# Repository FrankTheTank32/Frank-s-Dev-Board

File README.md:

This respository includes the bill of materials (BOM), GRBR and DRL files for PCB manufacturing and specifications, as well as the entire project folder itself for importing into KiCAD.

The DevBoard is comprised of an RP2040 microcontroller, lights, 43 pins total, an IMU, and a nice silkscreen design. It resembles the shape of an "F" after the name frame, and has the meming frog, as that also starts with an "F". This development board is extremely useful if you're looking to have a highly functional (and highly energetic) microcontroller electronics maker experience.

PCB design in 2D

PCB design in 3D

ENJOY!!!

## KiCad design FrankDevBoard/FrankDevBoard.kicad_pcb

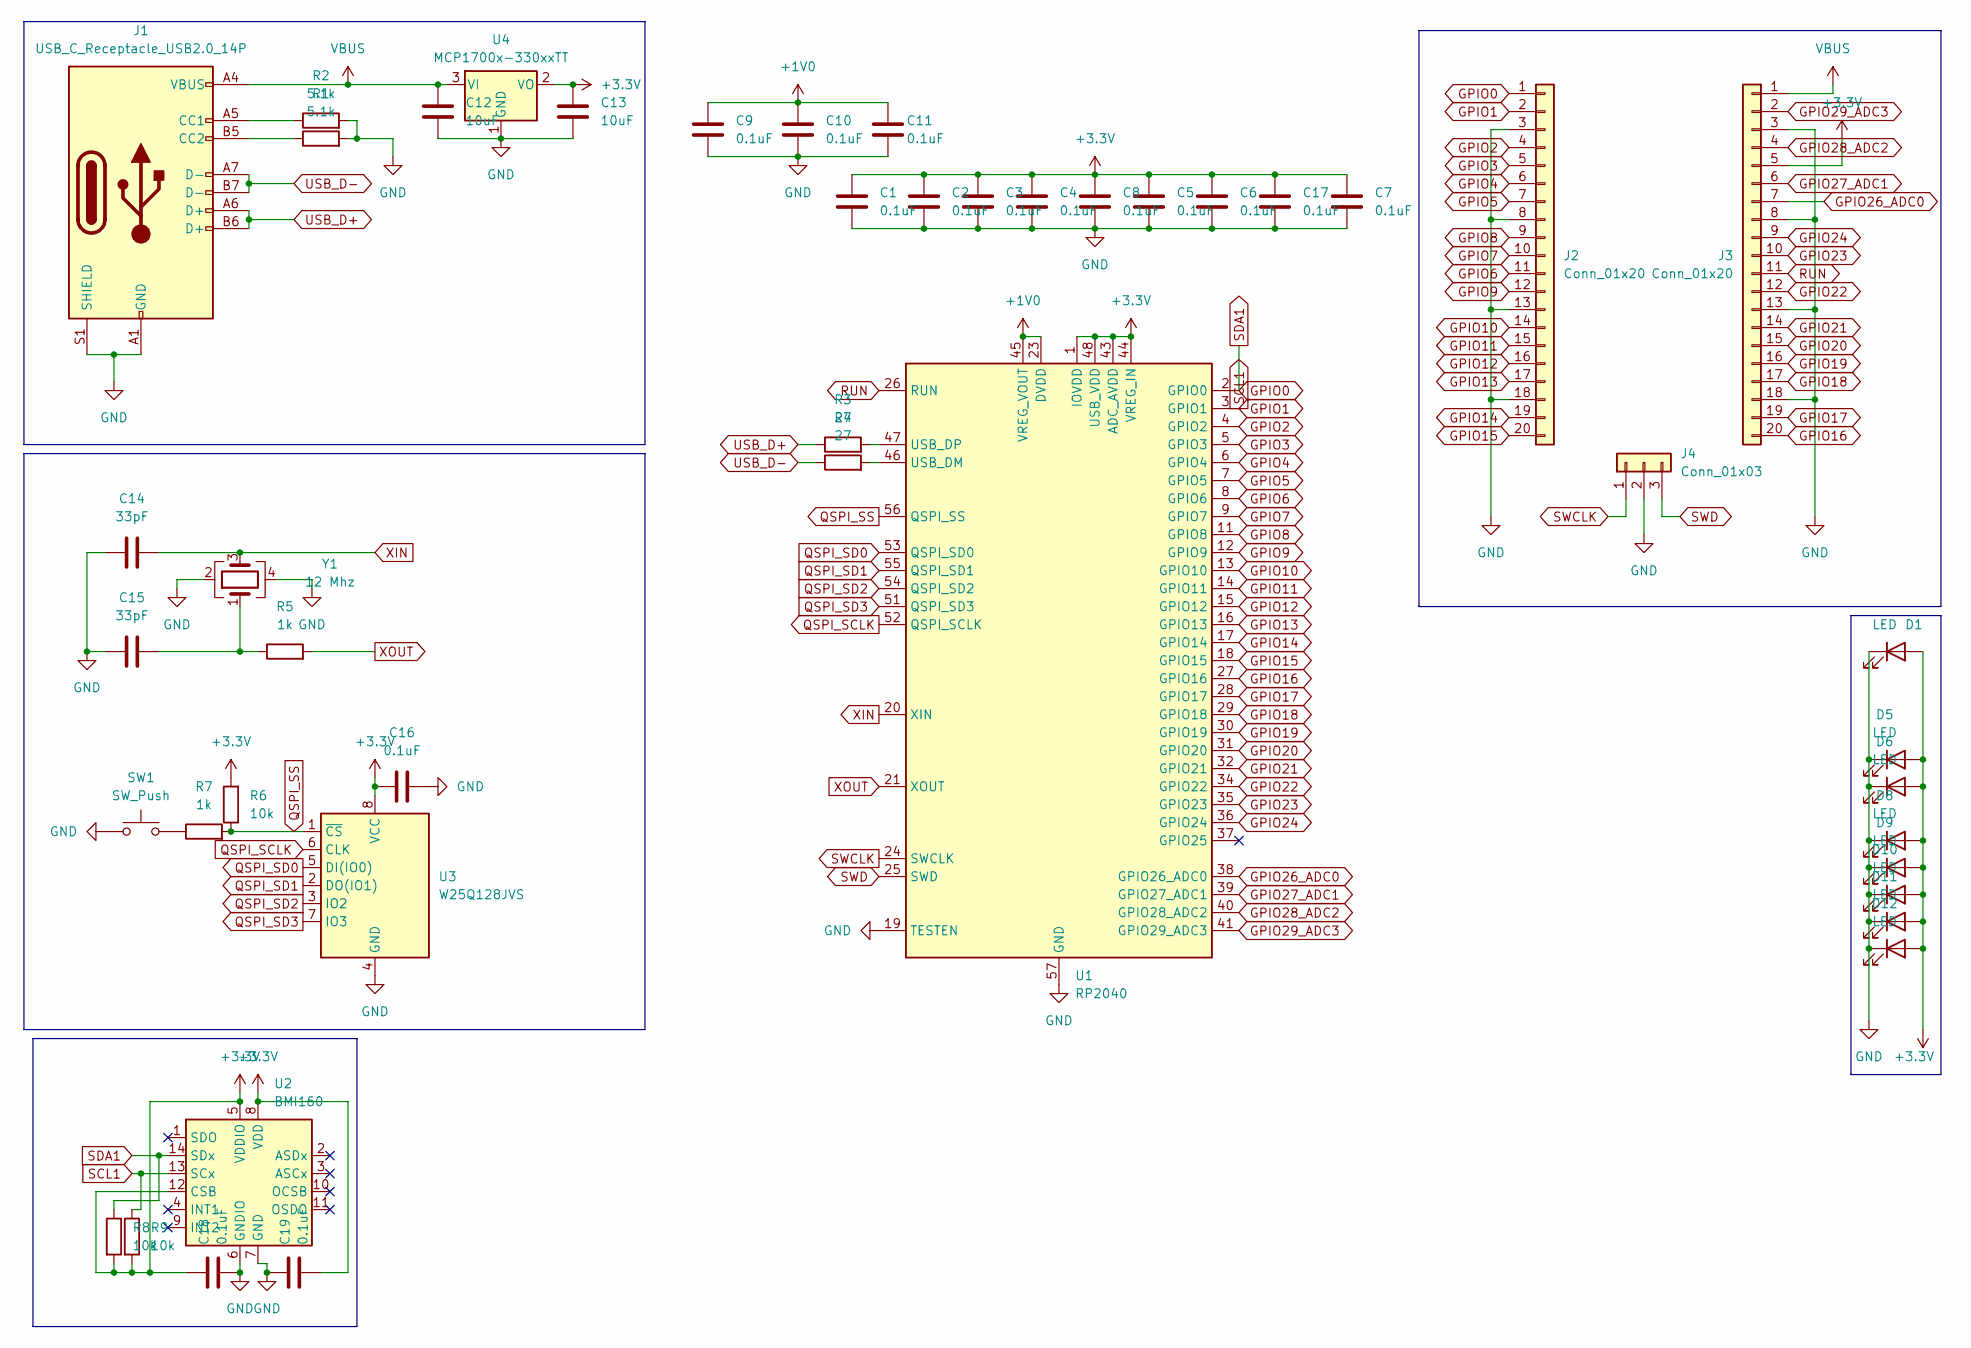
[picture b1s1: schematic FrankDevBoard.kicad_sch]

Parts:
C1, C2, C3, C4, C5, C6, C7, C8, C9, C10, C11, C16, C17, C18, C19: 0.1uF; C_0402_1005Metric
C12, C13: 10uF; C_0603_1608Metric
C14, C15: 33pF; C_0402_1005Metric
D1, D5, D6, D8, D9, D10, D11, D12: LED; LED_1210_3225Metric
J1: USB_C_Receptacle_USB2.0_14P; USB_C_Receptacle_HRO_TYPE-C-31-M-12
J2, J3: Conn_01x20; PinHeader_1x20_P2.54mm_Vertical
J4: Conn_01x03; PinHeader_1x03_P2.54mm_Vertical
R1, R2: 5.1k; R_0402_1005Metric
R3, R4: 27; R_0402_1005Metric
R5, R7: 1k; R_0402_1005Metric
R6, R8, R9: 10k; R_0402_1005Metric
SW1: SW_Push; SW_Push_SPST_NO_Alps_SKRK
U1: RP2040; QFN-56-1EP_7x7mm_P0.4mm_EP3.2x3.2mm
U2: BMI160; Bosch_LGA-14_3x2.5mm_P0.5mm
U3: W25Q128JVS; SON-8-1EP_3x2mm_P0.5mm_EP1.4x1.6mm
U4: MCP1700x-330xxTT; SOT-23
Y1: 12 Mhz; Crystal_SMD_3225-4Pin_3.2x2.5mm

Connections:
+1V0: C9.1, C10.1, C11.1, U1.23 (DVDD), U1.45 (VREG_VOUT), U1.50 (DVDD)
+3.3V: C1.1, C2.1, C3.1, C4.1, C5.1, C6.1, C7.1, C8.1, C13.1, C16.1, C17.1, C18.1, C19.2, D1.2 (A), D5.2 (A), D6.2 (A), D8.2 (A), D9.2 (A), D10.2 (A), D11.2 (A), D12.2 (A), J3.5, R6.2, R8.2, R9.2, U1.1 (IOVDD), U1.10 (IOVDD), U1.22 (IOVDD), U1.33 (IOVDD), U1.42 (IOVDD), U1.43 (ADC_AVDD), U1.44 (VREG_IN), U1.48 (USB_VDD), U1.49 (IOVDD), U2.5 (VDDIO), U2.8 (VDD), U2.12 (CSB), U3.8 (VCC), U4.2 (VO)
GND: C1.2, C2.2, C3.2, C4.2, C5.2, C6.2, C7.2, C8.2, C9.2, C10.2, C11.2, C12.2, C13.2, C14.1, C15.1, C16.2, C17.2, C18.2, C19.1, D1.1 (K), D5.1 (K), D6.1 (K), D8.1 (K), D9.1 (K), D10.1 (K), D11.1 (K), D12.1 (K), J1.A1 (GND), J1.A12 (GND), J1.B1 (GND), J1.B12 (GND), J1.S1 (SHIELD), J2.3, J2.8, J2.13, J2.18, J3.3, J3.8, J3.13, J3.18, J4.2, R1.2, R2.2, SW1.1, U1.19 (TESTEN), U1.57 (GND), U2.6 (GNDIO), U2.7 (GND), U3.4 (GND), U4.1 (GND), Y1.2, Y1.4
GPIO0: J2.1, R8.1, U1.2 (GPIO0), U2.14 (SDx)
GPIO1: J2.2, R9.1, U1.3 (GPIO1), U2.13 (SCx)
GPIO2: J2.4, U1.4 (GPIO2)
GPIO3: J2.5, U1.5 (GPIO3)
GPIO4: J2.6, U1.6 (GPIO4)
GPIO5: J2.7, U1.7 (GPIO5)
GPIO6: J2.11, U1.8 (GPIO6)
GPIO7: J2.10, U1.9 (GPIO7)
GPIO8: J2.9, U1.11 (GPIO8)
GPIO9: J2.12, U1.12 (GPIO9)
GPIO10: J2.14, U1.13 (GPIO10)
GPIO11: J2.15, U1.14 (GPIO11)
GPIO12: J2.16, U1.15 (GPIO12)
GPIO13: J2.17, U1.16 (GPIO13)
GPIO14: J2.19, U1.17 (GPIO14)
GPIO15: J2.20, U1.18 (GPIO15)
GPIO16: J3.20, U1.27 (GPIO16)
GPIO17: J3.19, U1.28 (GPIO17)
GPIO18: J3.17, U1.29 (GPIO18)
GPIO19: J3.16, U1.30 (GPIO19)
GPIO20: J3.15, U1.31 (GPIO20)
GPIO21: J3.14, U1.32 (GPIO21)
GPIO22: J3.12, U1.34 (GPIO22)
GPIO23: J3.10, U1.35 (GPIO23)
GPIO24: J3.9, U1.36 (GPIO24)
GPIO26_ADC0: J3.7, U1.38 (GPIO26_ADC0)
GPIO27_ADC1: J3.6, U1.39 (GPIO27_ADC1)
GPIO28_ADC2: J3.4, U1.40 (GPIO28_ADC2)
GPIO29_ADC3: J3.2, U1.41 (GPIO29_ADC3)
unnamed: C15.2, R5.1, Y1.1
unnamed: J1.A5 (CC1), R2.1
unnamed: J1.B5 (CC2), R1.1
unnamed: R7.1, SW1.2
unnamed: R4.2, U1.46 (USB_DM)
unnamed: R3.2, U1.47 (USB_DP)
QSPI_SCLK: U1.52 (QSPI_SCLK), U3.6 (CLK)
QSPI_SD0: U1.53 (QSPI_SD0), U3.5 (DI(IO0))
QSPI_SD1: U1.55 (QSPI_SD1), U3.2 (DO(IO1))
QSPI_SD2: U1.54 (QSPI_SD2), U3.3 (IO2)
QSPI_SD3: U1.51 (QSPI_SD3), U3.7 (IO3)
QSPI_SS: R6.1, R7.2, U1.56 (QSPI_SS), U3.1 (~CS)
RUN: J3.11, U1.26 (RUN)
SWCLK: J4.1, U1.24 (SWCLK)
SWD: J4.3, U1.25 (SWD)
USB_D+: J1.A6 (D+), J1.B6 (D+), R3.1
USB_D-: J1.A7 (D-), J1.B7 (D-), R4.1
VBUS: C12.1, J1.A4 (VBUS), J1.A9 (VBUS), J1.B4 (VBUS), J1.B9 (VBUS), J3.1, U4.3 (VI)
XIN: C14.2, U1.20 (XIN), Y1.3
XOUT: R5.2, U1.21 (XOUT)

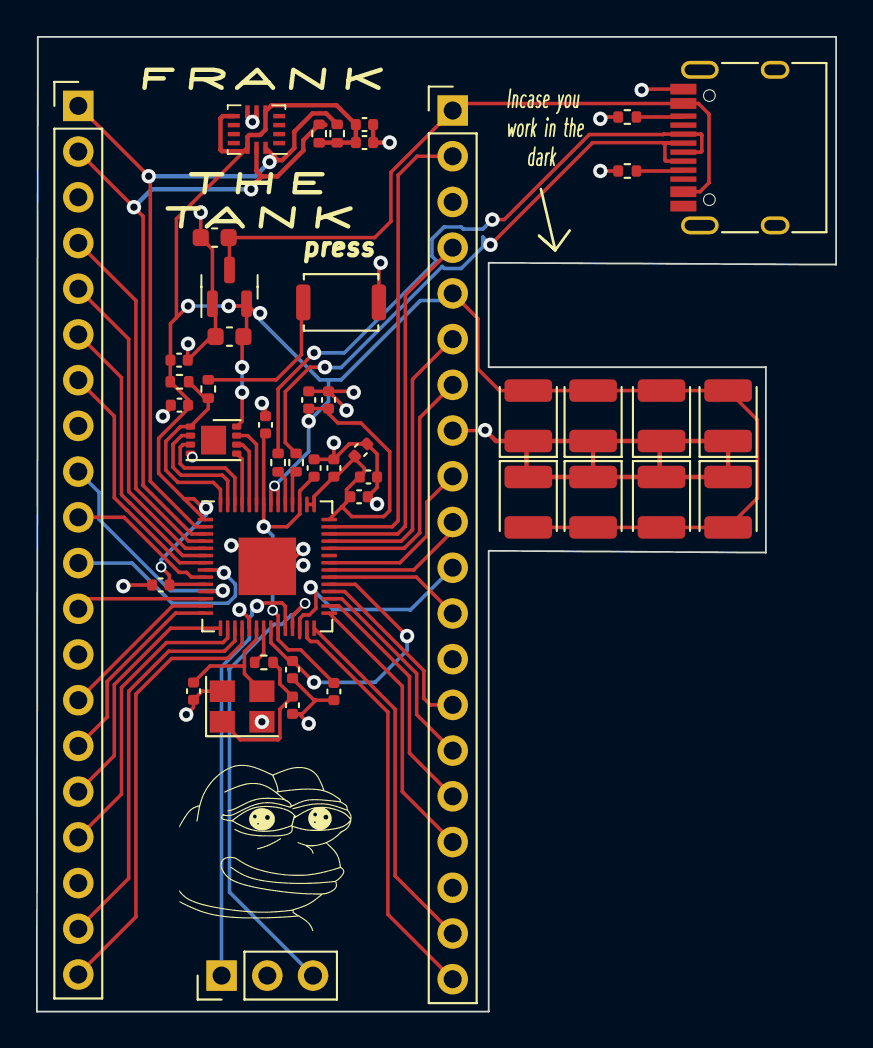
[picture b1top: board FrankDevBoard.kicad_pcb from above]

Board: 2 copper layers, 44.4 x 54.1 mm, 46 parts (0 on the bottom side), 52 nets.
